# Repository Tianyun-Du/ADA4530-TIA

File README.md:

************************************
Author:  Tianyun Du
Date:    March 15 2025
************************************
Discription:
This circuit is designed for precise current measurement.
For me is to measure the intensity of scintillator under X-ray radiation.
The photodiode I used is an HAMAMATSU S1227-1010BR.
The feedback resistance and capacitor used in these two Op Amp are calculated from the online design tool "Photodiode Circuit Design Wizard".
Website: https://tools.analog.com/en/photodiode/
ATTENTION:
IF YOU USE ANOTHER PHOTODIODE, RE-DESIGN THIS CIRCUIT WITH THIS TOOL.
THE PACKAGE OF THESE RESISTANCE AND CAPACITOR ARE "0805".
*************************************

************************************
************POWER SUPPLY************
************************************
USE INTERNAL POWER SUPPLY

The power supply of these Op Amps are ±5V (from 12V), you can also find this design in my other repository.
Use two jumper cap to enable the power supply on board ("H1"&"H2"). You can introduce 12V input from "DC1" OR "P1".

OR....

USE EXTERNAL POWER SUPPLY

External linear power supply can be used for power supply, to obtain a power with lower ripple.
Connect the +5V/AGND/-5V to "P2".
Other voltage can be used like ±10V and ±15V based on the data sheet of ADA4530-1, but I have not test yet.
The website of datasheet:
https://www.analog.com/media/en/technical-documentation/user-guides/ada4530-1r-ebz_ug-865.pdf

*************************************
*********ANOTHER INFORMATION*********
*************************************
DO NOT WELDING THE 0R RESISTANCE IN R2!

DO NOT WELDING THE 0R RESISTANCE IN R2!

DO NOT WELDING THE 0R RESISTANCE IN R2!

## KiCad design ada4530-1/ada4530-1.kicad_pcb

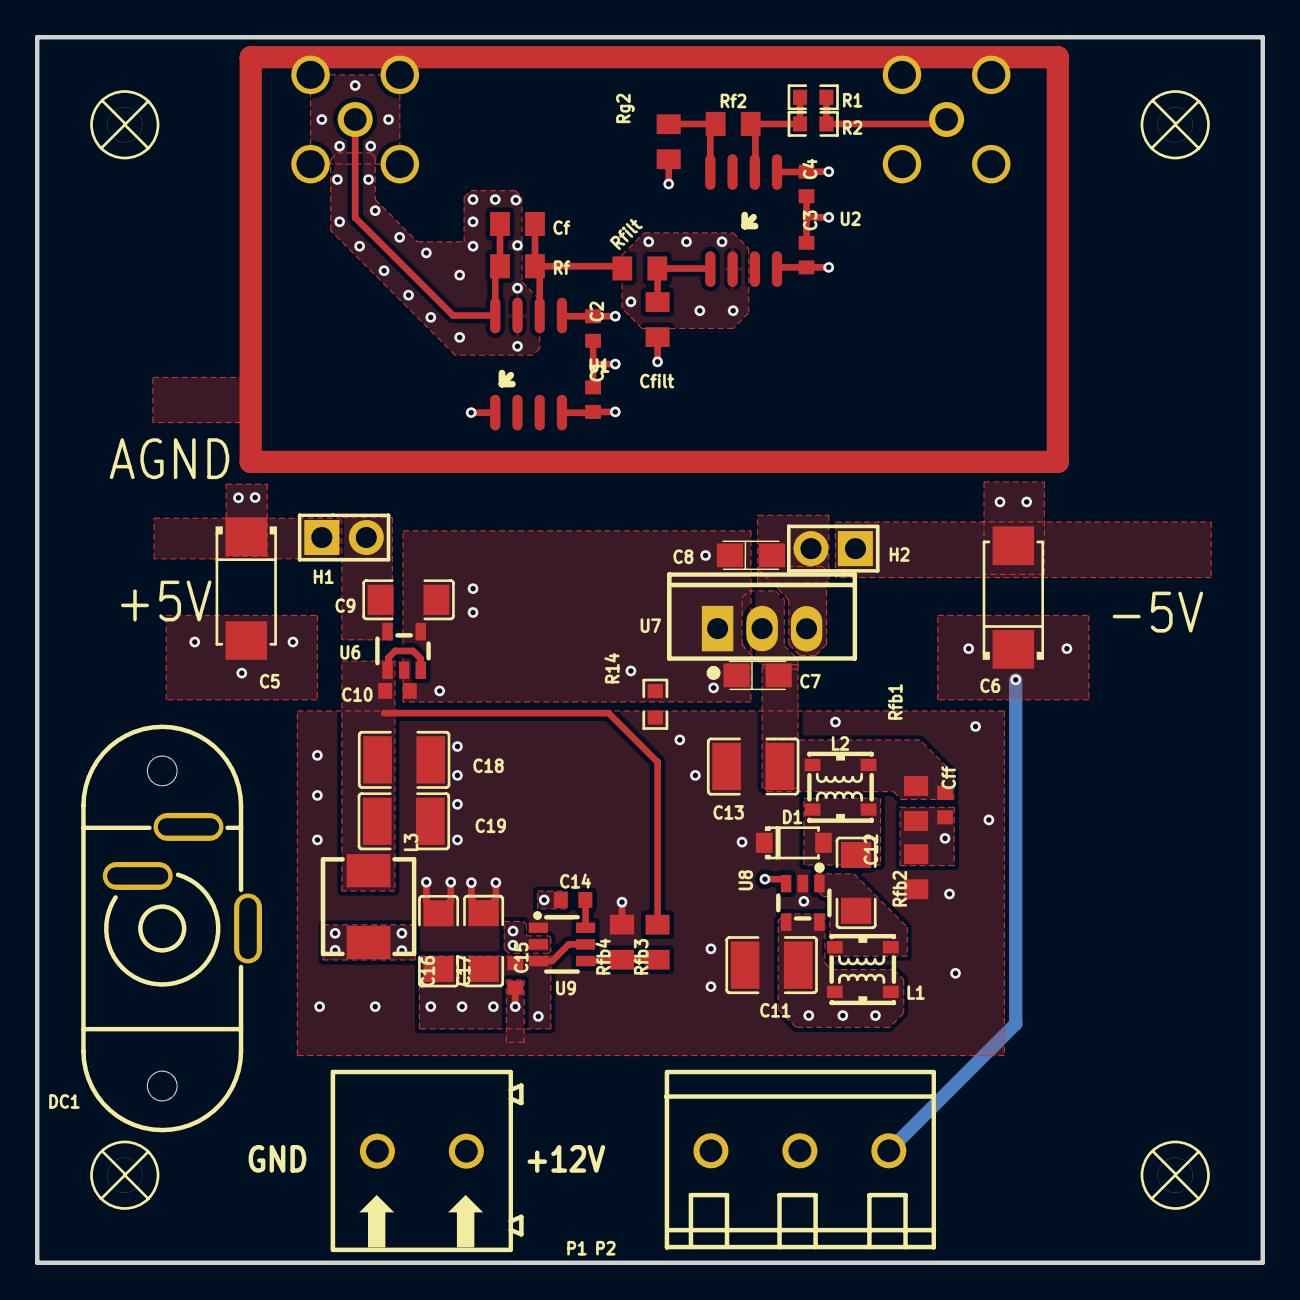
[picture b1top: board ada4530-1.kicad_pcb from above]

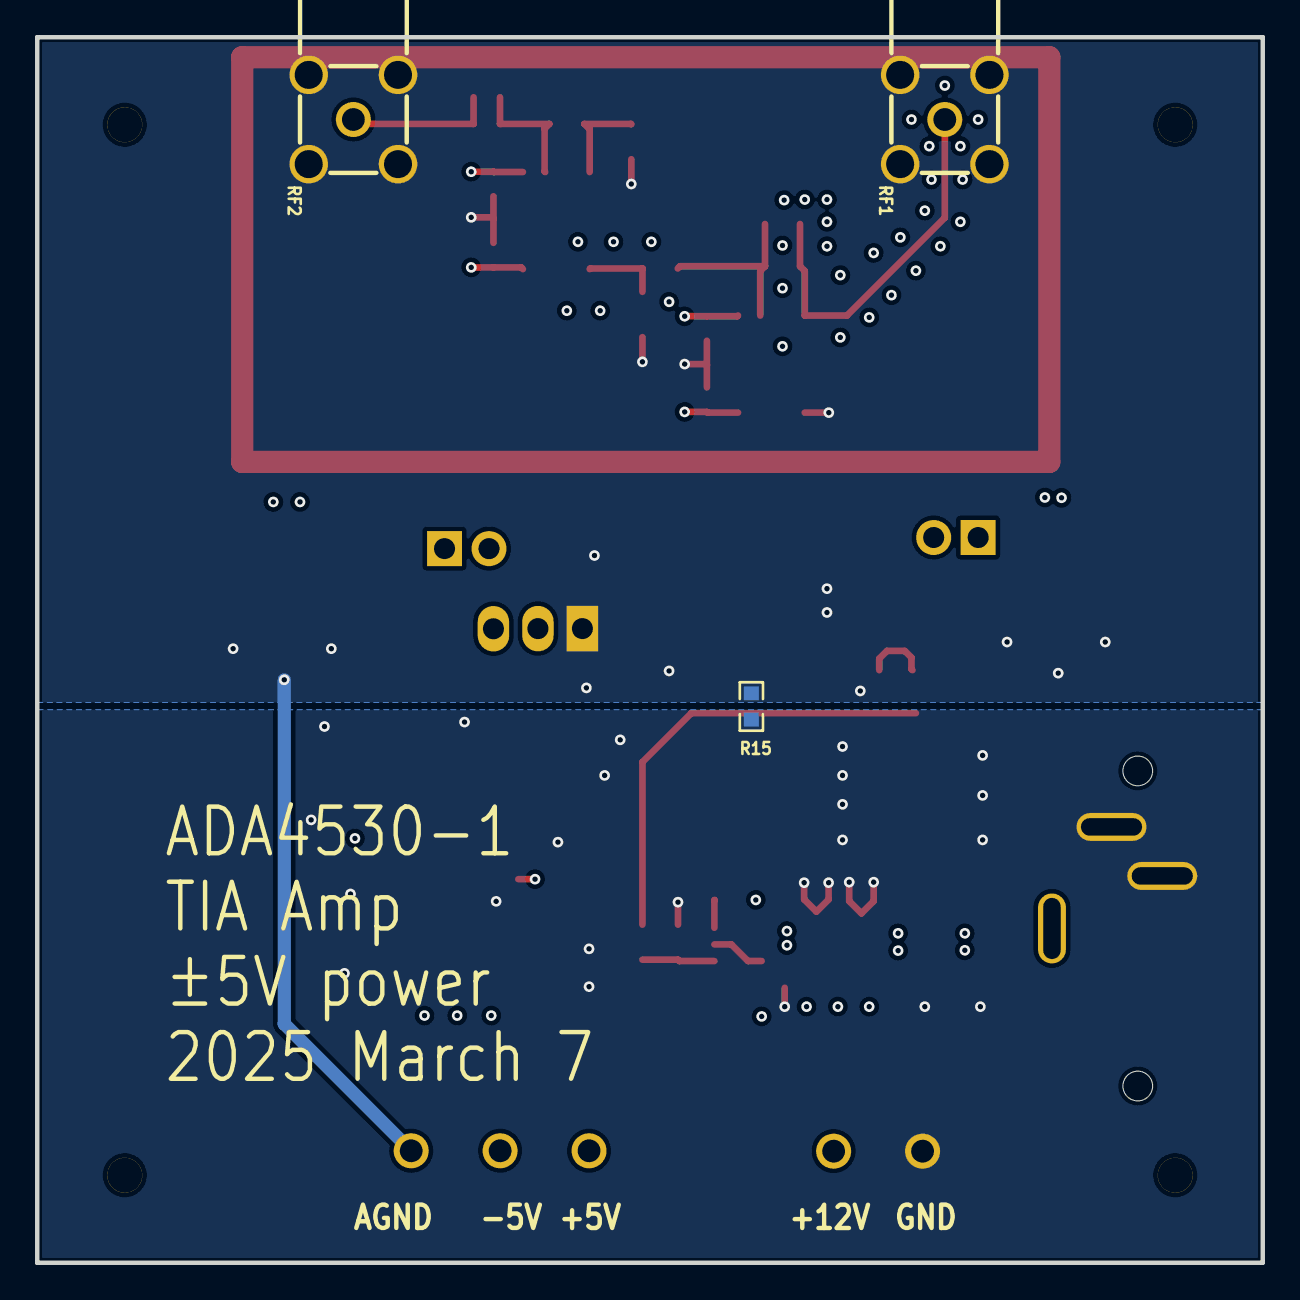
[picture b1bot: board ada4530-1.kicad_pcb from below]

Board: 4 copper layers, 70.0 x 70.0 mm, 55 parts (3 on the bottom side), 21 nets.

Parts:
C1, C2, C3, C4, C10, C14, C15: C0603
C5, C6: CAP-SMD_L6.0-W3.2-R-RD
C7, C8: CASE-A_3216
C9, C12, C16, C17: C1206
C11, C13, C18, C19: C1210
Cf: R0805
Cff: C0603
Cfilt: R0805
D1: SOD-123_L2.8-W1.8-LS3.7-RD
DC1: DC-IN-TH_DC-018
H1, H2: HDR-TH_2P-P2.54-V-M
L1, L2: IND-SMD_4P-L3.8-W3.5_BL
L3: IND-SMD_L5.4-W5.2_FXL0530
P1: CONN-TH_2P-P5.00_WJ500V-5.08-2P
P2: CONN-TH_3P-P5.00_WJ500V-5.08-3P
R1, R2, R14, R15: R0603
RF1, RF2: SMA-TH_BWSMA-KWE-Z001
Rf, Rf2: R0805
Rfb1, Rfb2, Rfb3, Rfb4: R0805
Rfilt: R0805
Rg2: R0805
SCREW1, SCREW2, SCREW3, SCREW4: M2螺丝
U1, U2: SOIC-8_L4.9-W3.9-P1.27-LS6.0-BL
U6: SOT-23-5_L2.9-W1.6-P0.95-LS2.8-BL
U7: TO-220-3_L10.0-W4.5-P2.54-L
U8: SOT-23-5_L2.9-W1.6-P0.95-LS2.8-BR
U9: SOT-23-6_L2.9-W1.6-P0.95-LS2.8-BR

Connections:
$1N1239: Cf.1, Rf.1, Rfilt.2, U1.6
$1N1441: Cfilt.2, Rfilt.1, U2.1
$1N1504: R1.1, R2.2, Rf2.1, U2.6
$1N1510: Rf2.2, Rg2.1, U2.8
$1N1693: R1.2, R2.1, RF2.5
$1N3691: C12.1, L1.2, L1.3, U8.1
$1N3697: Cff.1, Rfb1.1, Rfb2.2, U8.3
$1N3853: C12.2, D1.2, L2.1, L2.4
$1N5017: C14.2, L3.2, U9.2
$1N5032: C14.1, U9.6
$1N5055: Rfb3.1, Rfb4.2, U9.4
+5V: C2.2, C4.2, C5.1, H1.1, P2.1, U1.5, U2.5
+5VOUT: C9.2, H1.2, U6.5
+6.5V: C10.2, C18.2, C19.2, L3.1, Rfb3.2, U6.1, U6.3
+12V: C11.2, C15.2, C16.1, C17.1, DC1.1, L1.1, L1.4, P1.1, U8.4, U8.5, U9.3, U9.5
-5V: C1.2, C3.1, C6.2, H2.1, P2.2, U1.4, U2.4
-5VOUT: C8.2, H2.2, U7.3
-6V: C7.2, C13.2, Cff.2, L2.2, L2.3, Rfb1.2, U7.2
AGND: C1.1, C2.1, C3.2, C4.1, C5.2, C6.1, C7.1, C8.1, C9.1, C10.1, Cfilt.1, P2.3, R14.1, R15.1, RF1.1, RF1.2, RF1.3, RF1.4, RF2.1, RF2.2, RF2.3, RF2.4, Rg2.2, U1.1, U6.2, U6.4, U7.1
GND: C11.1, C13.1, C15.1, C16.2, C17.2, C18.1, C19.1, D1.1, DC1.2, DC1.3, P1.2, R14.2, R15.2, Rfb2.1, Rfb4.1, U8.2, U9.1
IN-: Cf.2, RF1.5, Rf.2, U1.8

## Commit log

2025-03-15 upload files
2025-11-28 Fix duplicate warning in README.md
